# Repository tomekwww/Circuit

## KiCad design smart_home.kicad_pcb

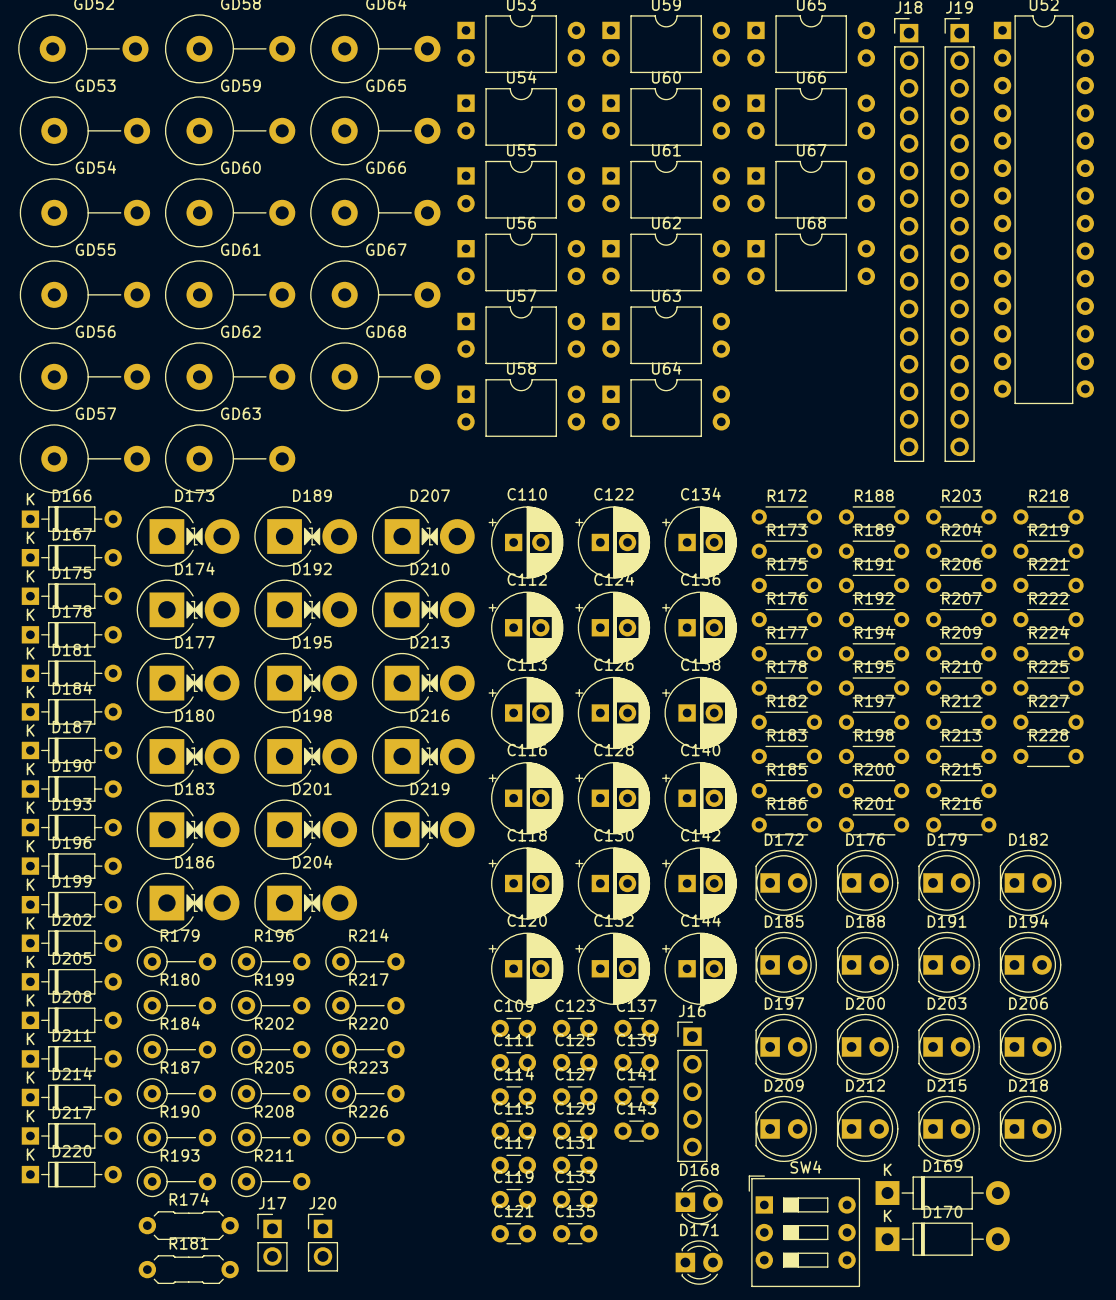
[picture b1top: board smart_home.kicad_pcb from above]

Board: 2 copper layers, 188 parts (0 on the bottom side), 100 nets, no tracks yet.

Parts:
C109, C111, C114, C115, C117, C119, C121, C123, C125, C127, C129, C131, C133, C135, C137, C139, C141, C143: 100n; C_Disc_D3.0mm_W1.6mm_P2.50mm
C110, C112, C113, C116, C118, C120, C122, C124, C126, C128, C130, C132, C134, C136, C138, C140, C142, C144: 100u; CP_Radial_D6.3mm_P2.50mm
D166, D167, D175, D178, D181, D184, D187, D190, D193, D196, D199, D202, D205, D208, D211, D214, D217, D220: 1.1; D_DO-35_SOD27_P7.62mm_Horizontal
D168, D171: 2,0; LED_D3.0mm
D169, D170: 0,5; D_DO-41_SOD81_P10.16mm_Horizontal
D172, D176, D179, D182, D185, D188, D191, D194, D197, D200, D203, D206, D209, D212, D215, D218: 2; LED_D5.0mm
D173, D174, D177, D180, D183, D186, D189, D192, D195, D198, D201, D204, D207, D210, D213, D216, D219: 8,55; D_DO-201AD_P5.08mm_Vertical_TVS
GD52, GD53, GD54, GD55, GD56, GD57, GD58, GD59, GD60, GD61, GD62, GD63, GD64, GD65, GD66, GD67, GD68: 90; R_Axial_DIN0617_L17.0mm_D6.0mm_P7.62mm_Vertical
J16: Pin Header 1x5 Male; PinHeader_1x05_P2.54mm_Vertical
J17: INT Pin Header 1x2 Male; PinHeader_1x02_P2.54mm_Vertical
J18: OUT Pin Hrader 1x16 Male; PinHeader_1x16_P2.54mm_Vertical
J19: IN Pin Header 1x16 Male; PinHeader_1x16_P2.54mm_Vertical
J20: Pin Header 1x2 Male; PinHeader_1x02_P2.54mm_Vertical
R172, R173, R175, R176, R177, R178: 10k; R_Axial_DIN0204_L3.6mm_D1.6mm_P5.08mm_Horizontal
R174, R181: 1.6k; R_Axial_DIN0207_L6.3mm_D2.5mm_P7.62mm_Horizontal
R179, R180, R184, R187, R190, R193, R196, R199, R202, R205, R208, R211, R214, R217, R220, R223, R226: 1; R_Axial_DIN0207_L6.3mm_D2.5mm_P5.08mm_Vertical
R182, R185, R188, R191, R194, R197, R200, R203, R206, R209, R212, R215, R218, R221, R224, R227: 1k; R_Axial_DIN0204_L3.6mm_D1.6mm_P5.08mm_Horizontal
R183, R186, R189, R192, R195, R198, R201, R204, R207, R210, R213, R216, R219, R222, R225, R228: 4.7k; R_Axial_DIN0204_L3.6mm_D1.6mm_P5.08mm_Horizontal
SW4: DIP Switch 1x3; SW_DIP_SPSTx03_Slide_9.78x9.8mm_W7.62mm_P2.54mm
U52: MCP23017; DIP-28_W7.62mm
U53, U54, U55, U56, U57, U58, U59, U60, U61, U62, U63, U64, U65, U66, U67, U68: PC817; DIP-4_W10.16mm

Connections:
5V VCC: C109.2, C110.1, J16.5, R172.2, R173.2, R174.2, R175.2, R183.2, R186.2, R189.2, R192.2, R195.2, R198.2, R201.2, R204.2, R207.2, R210.2, R213.2, R216.2, R219.2, R222.2, R225.2, R228.2, SW4.1, SW4.2, SW4.3, U52.9 (VDD)
/Elektrozaczepy/GND VCC: D170.1 (K), J16.4
/Input buttons 1/SCK: J16.3, R173.1, U52.12 (SCK)
/Input buttons 1/SDA: J16.2, R172.1, U52.13 (SDA)
/Input buttons 4/INT A: D166.2 (A), J17.2
/Input buttons 4/INT B: D167.2 (A), J17.1
Earth: D173.2 (A2), D174.2 (A2), D177.2 (A2), D180.2 (A2), D183.2 (A2), D186.2 (A2), D189.2 (A2), D192.2 (A2), D195.2 (A2), D198.2 (A2), D201.2 (A2), D204.2 (A2), D207.2 (A2), D210.2 (A2), D213.2 (A2), D216.2 (A2), D219.2 (A2), GD52.1, GD53.1, GD54.1, GD55.1, GD56.1, GD57.1, GD58.1, GD59.1, GD60.1, GD61.1, GD62.1, GD63.1, GD64.1, GD65.1, GD66.1, GD67.1, GD68.1
unnamed: D166.1 (K), U52.19 (INTB)
unnamed: D167.1 (K), U52.20 (INTA)
unnamed: D168.2 (A), R174.1
unnamed: C109.1, C110.2, C111.1, C112.2, C115.1, C116.2, C117.1, C118.2, C119.1, C120.2, C121.1, C122.2, C123.1, C124.2, C125.1, C126.2, C127.1, C128.2, C129.1, C130.2, C131.1, C132.2, C133.1, C134.2, C135.1, C136.2, C137.1, C138.2, C139.1, C140.2, C141.1, C142.2, C143.1, C144.2, D168.1 (K), D170.2 (A), R176.1, R177.1, R178.1, U52.10 (VSS), U53.3, U54.3, U55.3, U56.3, U57.3, U58.3, U59.3, U60.3, U61.3, U62.3, U63.3, U64.3, U65.3, U66.3, U67.3, U68.3
unnamed: C113.2, C114.1, D169.2 (A), D171.1 (K), D173.1 (A1), R179.1
unnamed: D171.2 (A), R181.2
unnamed: D172.2 (A), U53.2
unnamed: D172.1 (K), D174.1 (A1), D175.2 (A), R180.2
unnamed: D176.2 (A), U54.2
unnamed: D176.1 (K), D177.1 (A1), D178.2 (A), R184.2
unnamed: D179.2 (A), U55.2
unnamed: D179.1 (K), D180.1 (A1), D181.2 (A), R187.2
unnamed: D182.2 (A), U56.2
unnamed: D182.1 (K), D183.1 (A1), D184.2 (A), R190.2
unnamed: D185.2 (A), U57.2
unnamed: D185.1 (K), D186.1 (A1), D187.2 (A), R193.2
unnamed: D188.2 (A), U58.2
unnamed: D188.1 (K), D189.1 (A1), D190.2 (A), R196.2
unnamed: D191.2 (A), U59.2
unnamed: D191.1 (K), D192.1 (A1), D193.2 (A), R199.2
unnamed: D194.2 (A), U60.2
unnamed: D194.1 (K), D195.1 (A1), D196.2 (A), R202.2
unnamed: D197.2 (A), U61.2
unnamed: D197.1 (K), D198.1 (A1), D199.2 (A), R205.2
unnamed: D200.2 (A), U62.2
unnamed: D200.1 (K), D201.1 (A1), D202.2 (A), R208.2
unnamed: D202.1 (K), R209.2
unnamed: D203.2 (A), U63.2
unnamed: D203.1 (K), D204.1 (A1), D205.2 (A), R211.2
unnamed: D206.2 (A), U64.2
unnamed: D206.1 (K), D207.1 (A1), D208.2 (A), R214.2
unnamed: D209.2 (A), U65.2
unnamed: D209.1 (K), D210.1 (A1), D211.2 (A), R217.2
unnamed: D212.2 (A), U66.2
unnamed: D212.1 (K), D213.1 (A1), D214.2 (A), R220.2
unnamed: D215.2 (A), U67.2
unnamed: D215.1 (K), D216.1 (A1), D217.2 (A), R223.2
unnamed: D218.2 (A), U68.2
unnamed: D218.1 (K), D219.1 (A1), D220.2 (A), R226.2
unnamed: J18.1, J18.2, J18.3, J18.4, J18.5, J18.6, J18.7, J18.8, J18.9, J18.10, J18.11, J18.12, J18.13, J18.14, J18.15, J18.16, R179.2
unnamed: J19.16, R180.1
unnamed: J19.15, R184.1
unnamed: J19.14, R187.1
unnamed: J19.13, R190.1
unnamed: J19.12, R193.1
unnamed: J19.11, R196.1
unnamed: J19.10, R199.1
unnamed: J19.9, R202.1
unnamed: J19.8, R205.1
unnamed: J19.7, R208.1
unnamed: J19.6, R211.1
unnamed: J19.5, R214.1
unnamed: J19.4, R217.1
unnamed: J19.3, R220.1
unnamed: J19.2, R223.1
unnamed: R182.1, U53.1
unnamed: R185.1, U54.1
unnamed: R188.1, U55.1
unnamed: R191.1, U56.1
unnamed: R194.1, U57.1
unnamed: R197.1, U58.1
unnamed: R200.1, U59.1
unnamed: R203.1, U60.1
unnamed: R206.1, U61.1
unnamed: R209.1, U62.1
unnamed: R212.1, U63.1
unnamed: R215.1, U64.1
unnamed: R218.1, U65.1
unnamed: R221.1, U66.1
unnamed: R224.1, U67.1
unnamed: R227.1, U68.1
unnamed: R176.2, SW4.4, U52.15 (A0)
unnamed: R177.2, SW4.5, U52.16 (A1)
unnamed: R178.2, SW4.6, U52.17 (A2)
unnamed: C143.2, C144.1, R228.1, U52.21 (GPA0), U68.4
unnamed: C141.2, C142.1, R225.1, U52.22 (GPA1), U67.4
unnamed: C139.2, C140.1, R222.1, U52.23 (GPA2), U66.4
unnamed: C137.2, C138.1, R219.1, U52.24 (GPA3), U65.4
unnamed: C135.2, C136.1, R216.1, U52.25 (GPA4), U64.4
unnamed: C133.2, C134.1, R213.1, U52.26 (GPA5), U63.4
unnamed: C131.2, C132.1, R210.1, U52.27 (GPA6), U62.4
unnamed: C129.2, C130.1, R207.1, U52.28 (GPA7), U61.4
unnamed: C127.2, C128.1, R204.1, U52.1 (GPB0), U60.4
unnamed: C125.2, C126.1, R201.1, U52.2 (GPB1), U59.4
unnamed: C123.2, C124.1, R198.1, U52.3 (GPB2), U58.4
unnamed: C121.2, C122.1, R195.1, U52.4 (GPB3), U57.4
unnamed: C119.2, C120.1, R192.1, U52.5 (GPB4), U56.4
unnamed: C117.2, C118.1, R189.1, U52.6 (GPB5), U55.4
unnamed: C115.2, C116.1, R186.1, U52.7 (GPB6), U54.4
unnamed: C111.2, C112.1, R183.1, U52.8 (GPB7), U53.4
Power +5,5V: C113.1, C114.2, D175.1 (K), D178.1 (K), D181.1 (K), D184.1 (K), D187.1 (K), D190.1 (K), D193.1 (K), D196.1 (K), D199.1 (K), D205.1 (K), D208.1 (K), D211.1 (K), D214.1 (K), D217.1 (K), D220.1 (K), J19.1, J20.2, R181.1, R182.2, R185.2, R188.2, R191.2, R194.2, R197.2, R200.2, R203.2, R206.2, R212.2, R215.2, R218.2, R221.2, R224.2, R226.1, R227.2
Power GND: D169.1 (K), J20.1
Reset: J16.1, R175.1, U52.18 (~RESET)

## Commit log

2024-04-22 Initial circuit
